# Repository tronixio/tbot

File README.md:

# DRAFT - TBOT 2 Wheels.

## Features.

- 2 Wheels.
- Continuous Servos Motors.
- Power 2xCells 18650 Lithium Ion Rechargeable Batteries, with charger embedded.
- [PARALLAX Small Robot Chassis.](https://www.parallax.com/product/700-00022)
- [PARALLAX Small Robot Whell and Tire.](https://www.parallax.com/product/28114)
- [PARALLAX 1" Tail Whell Ball.](https://www.parallax.com/product/700-00009)
- [PARALLAX Feedback 360 High Speed Servo.](https://www.parallax.com/product/900-00360)

## Kicad.

- [Charger 2x18650.](./0.kicad/charger)
- [TODO - MCU Board.](./0.kicad/mcu)
- [TODO - IR Line Follow.](./0.kicad/ir-line)

## Charger top.

## Charger bottom.

## Notes.

- TODO : Work in progress, prototype was not good, hardware, PCB and code can be rework.
- DRAFT : Prototype OK, last check schematic, PCB & code can be modify.

## DISCLAIMER.

THIS CODE IS PROVIDED WITHOUT ANY WARRANTY OR GUARANTEES.
USERS MAY USE THIS CODE FOR DEVELOPMENT AND EXAMPLE PURPOSES ONLY.
AUTHORS ARE NOT RESPONSIBLE FOR ANY ERRORS, OMISSIONS, OR DAMAGES THAT COULD
RESULT FROM USING THIS FIRMWARE IN WHOLE OR IN PART.

---

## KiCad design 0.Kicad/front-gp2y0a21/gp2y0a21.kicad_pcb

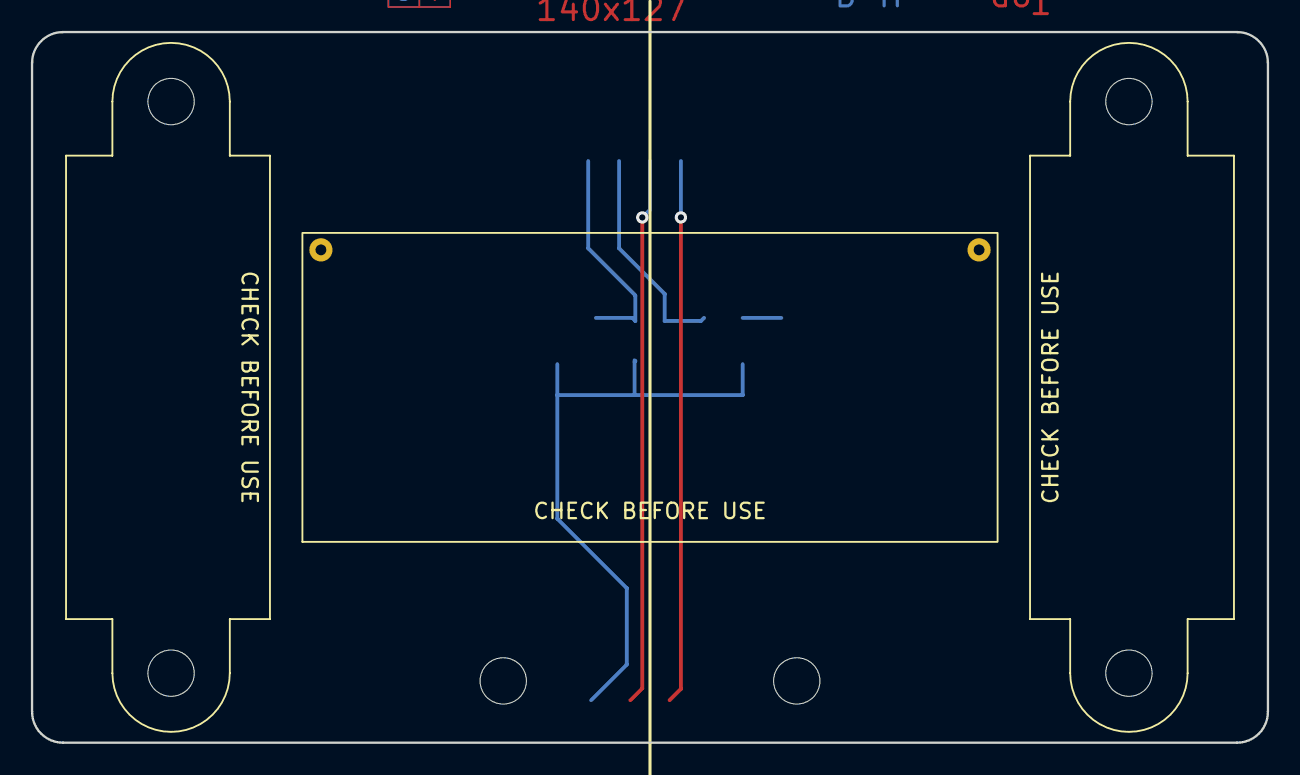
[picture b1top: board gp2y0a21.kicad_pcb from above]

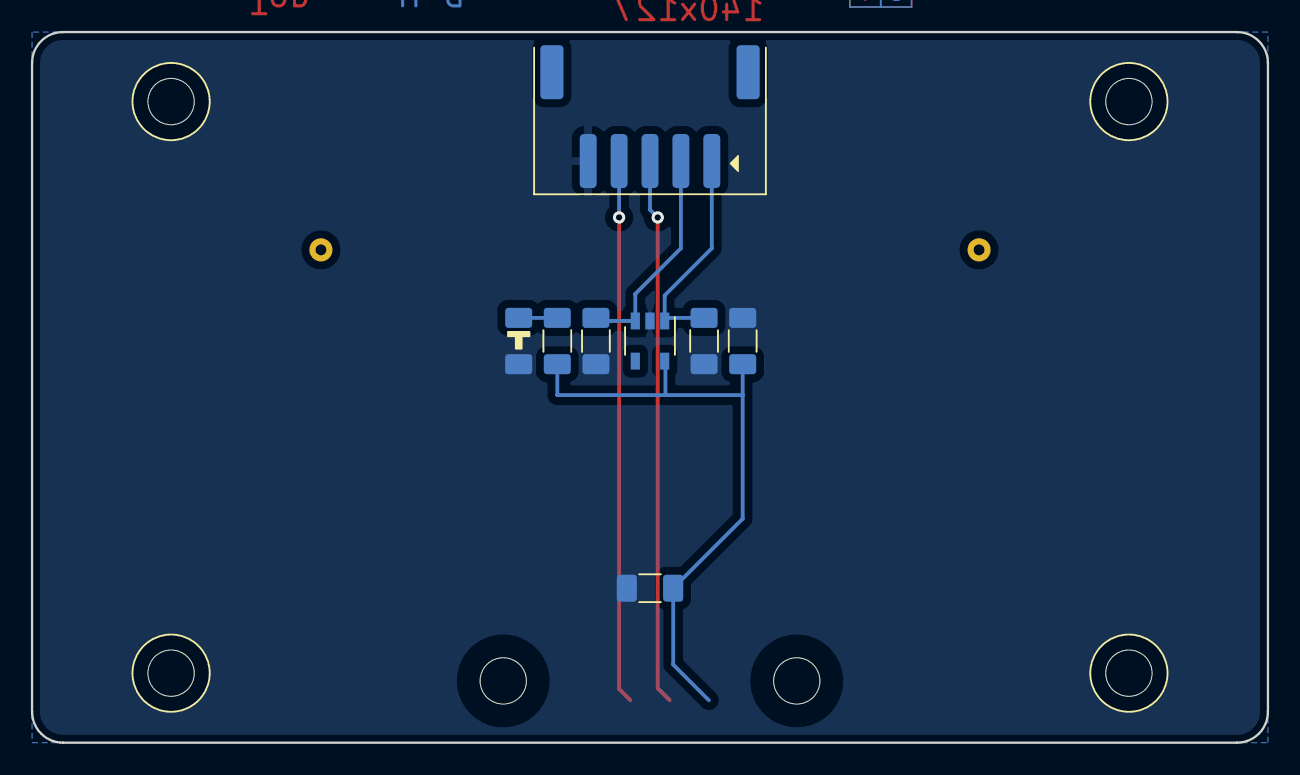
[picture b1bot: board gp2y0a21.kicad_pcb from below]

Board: 2 copper layers, 80.0 x 46.0 mm, 13 parts (8 on the bottom side), 5 nets.

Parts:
C1, C2, C3: C; CAPACITOR_1206
H1, H2: MOUNTING-HOLE-MASK-3MM; M3-MASK
HC1: HC-SR04
IC1: MCP1755-SOT23; SOT-23-5
IR1: SHARP-GP2Y0A21
IR2: SHARP-GP2Y0A41; SHARP-GP2Y0A21
K1: JST-PH-S5B-SM4-TB; JST-S5B-PH-SM4-TB
LED1: LED; LED_1206
R1, R2: R; RESISTOR_1206

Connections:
+5V: C2.1, IC1.5 (VOUT), R2.1
ENABLE: IC1.3 (~SHDN), K1.2, R1.1
GND: C1.2, C2.2, C3.2, IC1.2 (GND), K1.5, LED1.1 (K), R1.2
unnamed: LED1.2 (A), R2.2
VCC: C1.1, IC1.1 (VIN), K1.1

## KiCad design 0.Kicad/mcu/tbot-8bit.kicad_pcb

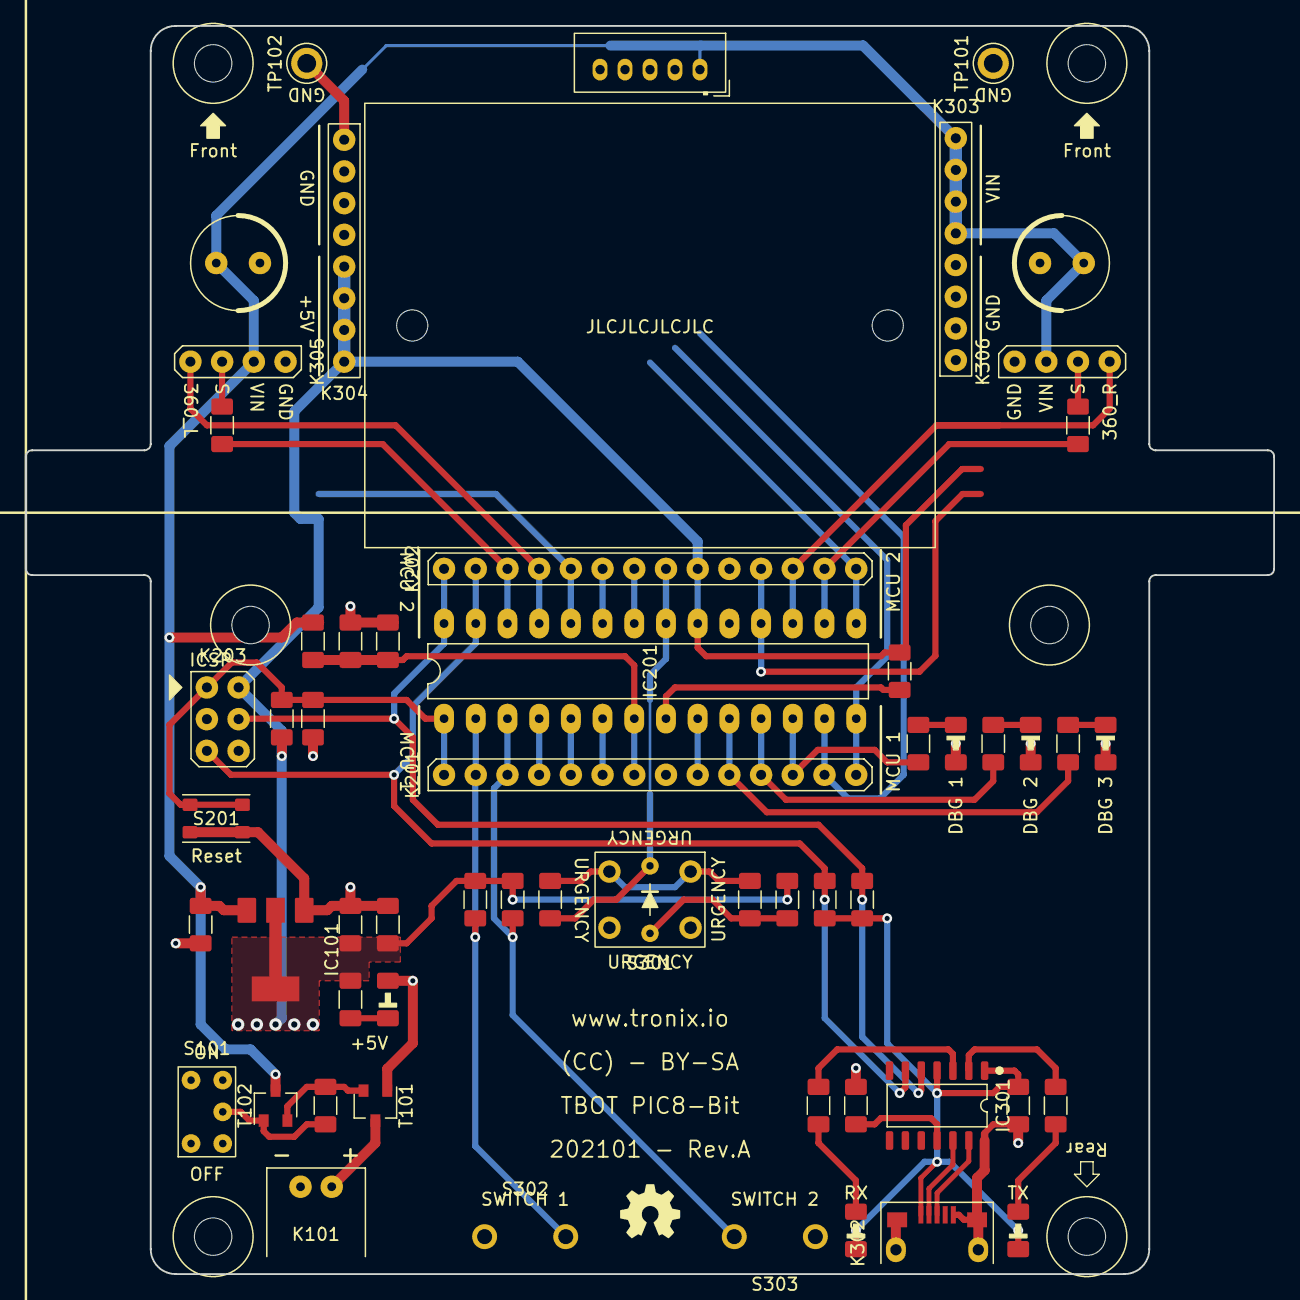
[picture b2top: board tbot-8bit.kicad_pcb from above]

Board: 2 copper layers, 100.0 x 100.0 mm, 64 parts (0 on the bottom side), 43 nets.

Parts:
BB301: BREADBOARD-170
C101, C102, C103, C104, C201, C202: C; CAPACITOR_1206
C301: 100n; CAPACITOR_1206
C302: 470n; CAPACITOR_1206
C303, C304: UVZ-220U-25V; CAPACITOR-ELECTROLYTIC-RADIAL-080-115-035
H1, H2, H3, H4, H5, H6: MOUNTING-HOLE-MASK-3MM; M3-MASK
IC101: TLV1117-50; SOT-223-3
IC201: PIC16F1778-IP; DIP-28-W762
IC301: MCP2221A-ISL; SOIC-SL-14
K101: MOLEX-5268-02
K201, K202: M20-999144x
K203: M20-998034x
K301: FRONT; JST-PH-B5B-K
K302: MICRO USB B; FCI-USB-TYPE-B-MICRO-THT
K303, K304: M20-782084x
K305: SERVO LEFT; M20-999044x
K306: SERVO RIGHT; M20-999044x
LED101: LED; LED_1206
LED301: URX; LED_1206
LED302: UTX; LED_1206
LED303: LED 3; LED_1206
LED304: LED 2; LED_1206
LED305: LED 1; LED_1206
R101, R102, R103, R104, R201, R303, R304, R307: R; RESISTOR_1206
R301, R302, R310, R311: 10K; RESISTOR_1206
R305, R306, R312, R313, R314: 5K6; RESISTOR_1206
R308, R309: 220R; RESISTOR_1206
S101: E-SWITCH-200USP1T1A1M2RE; E-SWITCH-200USPXT1A1M2RE
S201: ALPS-SKRPAC
S301: URGENCY; E-SWITCH-TL1240XQ1JXXX
S302: SWITCH 1; CK-PTS635S-THT
S303: SWITCH 2; CK-PTS635S-THT
T101, T102: DMP2305U; SOT-23-3
TP101, TP102: GND; KEYSTONE-5006

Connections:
+5V: C103.1, C104.1, C201.1, IC101.2 (VO), IC201.20 (VDD), K202.9, K203.2, K304.1, K304.2, K304.3, K304.4, R104.2, R201.2, R303.2, R310.2, R311.2
BATTERY_SENSE: C101.1, IC201.7 (RA5), K201.7, R101.1, R103.2
GND: C101.2, C102.2, C103.2, C104.2, C201.2, C202.2, C301.2, C302.2, C303.2, C304.2, IC101.1 (GND), IC201.8 (VSS), IC201.19 (VSS), IC301.14 (VSS), K101.1, K201.8, K202.10, K203.3, K301.5, K302.5 (GND), K302.6 (SHIELD), K303.5, K303.6, K303.7, K303.8, K304.5, K304.6, K304.7, K304.8, K305.1, K306.1, LED101.1 (K), LED303.1 (K), LED304.1 (K), LED305.1 (K), R103.1, S101.1, S201.1, S201.2, S301.3, S301.4, S302.1, S303.1, T101.1 (G), TP101.1, TP102.1
unnamed: C302.1, IC301.11 (VUSB)
unnamed: IC201.4 (RA2), K201.4
unnamed: IC201.5 (RA3), K201.5
unnamed: IC201.6 (RA4), K201.6
unnamed: IC201.9 (RA7/CLKI), K201.9
unnamed: IC301.2 (GP0), R306.1
unnamed: IC301.3 (GP1), R305.1
unnamed: IC301.12 (D-), K302.2 (D-)
unnamed: IC301.13 (D+), K302.3 (D+)
unnamed: K305.3, R308.2
unnamed: K306.3, R309.2
unnamed: LED101.2 (A), R104.1
unnamed: LED301.1 (K), R305.2
unnamed: LED302.1 (K), R306.2
unnamed: LED303.2 (A), R312.1
unnamed: LED304.2 (A), R313.1
unnamed: LED305.2 (A), R314.1
unnamed: R102.1, S101.2, T102.1 (G)
unnamed: R102.2, T101.2 (S), T102.2 (S)
unnamed: R303.1, R304.2, S301.6 (A)
unnamed: R304.1, R307.1, S301.1, S301.2
RA0/SWITCH_1: IC201.2 (RA0), K201.2, R310.1, S302.2
RA1/SWITCH_2: IC201.3 (RA1), K201.3, R311.1, S303.2
RA7/LED_3: IC201.10 (RA6/CLKO), K201.10, R312.2
RB0/URGENCY: IC201.21 (RB0), K202.8, R307.2, S301.5 (C)
RB4/360_L: IC201.25 (RB4), K202.4, K305.4
RB5/SERVO_L: IC201.26 (RB5), K202.3, R308.1
RB6/PGC/URX: IC201.27 (PGC/RB6), IC301.6 (UTx), K202.2, K203.5, R302.1
RB7/PGD/UTX: IC201.28 (PGD/RB7), IC301.5 (URx), K202.1, K203.4, R301.1
RC0/LED_2: IC201.11 (RC0), K201.11, R313.2
RC1/LED_1: IC201.12 (RC1), K201.12, R314.2
RC2/ENABLE: IC201.13 (RC2), K201.13, K301.2
RC3/TRIGGER/SCL: IC201.14 (RC3), K201.14, K301.3
RC4/ECHO/SDA: IC201.15 (RC4), K202.14, K301.4
RC5/SERVO_R: IC201.16 (RC5), K202.13, R309.1
RC6/360_R: IC201.17 (RC6), K202.12, K306.4
VBAT: K101.2, T101.3 (D)
VIN: C102.1, C303.1, C304.1, IC101.3 (VI), K301.1, K303.1, K303.2, K303.3, K303.4, K305.2, K306.2, R101.2, T102.3 (D)
VUSB: C301.1, IC301.1 (VDD), IC301.4 (~RESET), K302.1 (VBUS), LED301.2 (A), LED302.2 (A), R301.2, R302.2
~MCLR: C202.1, IC201.1 (RE3/~MCLR), K201.1, K203.1, R201.1, S201.3, S201.4

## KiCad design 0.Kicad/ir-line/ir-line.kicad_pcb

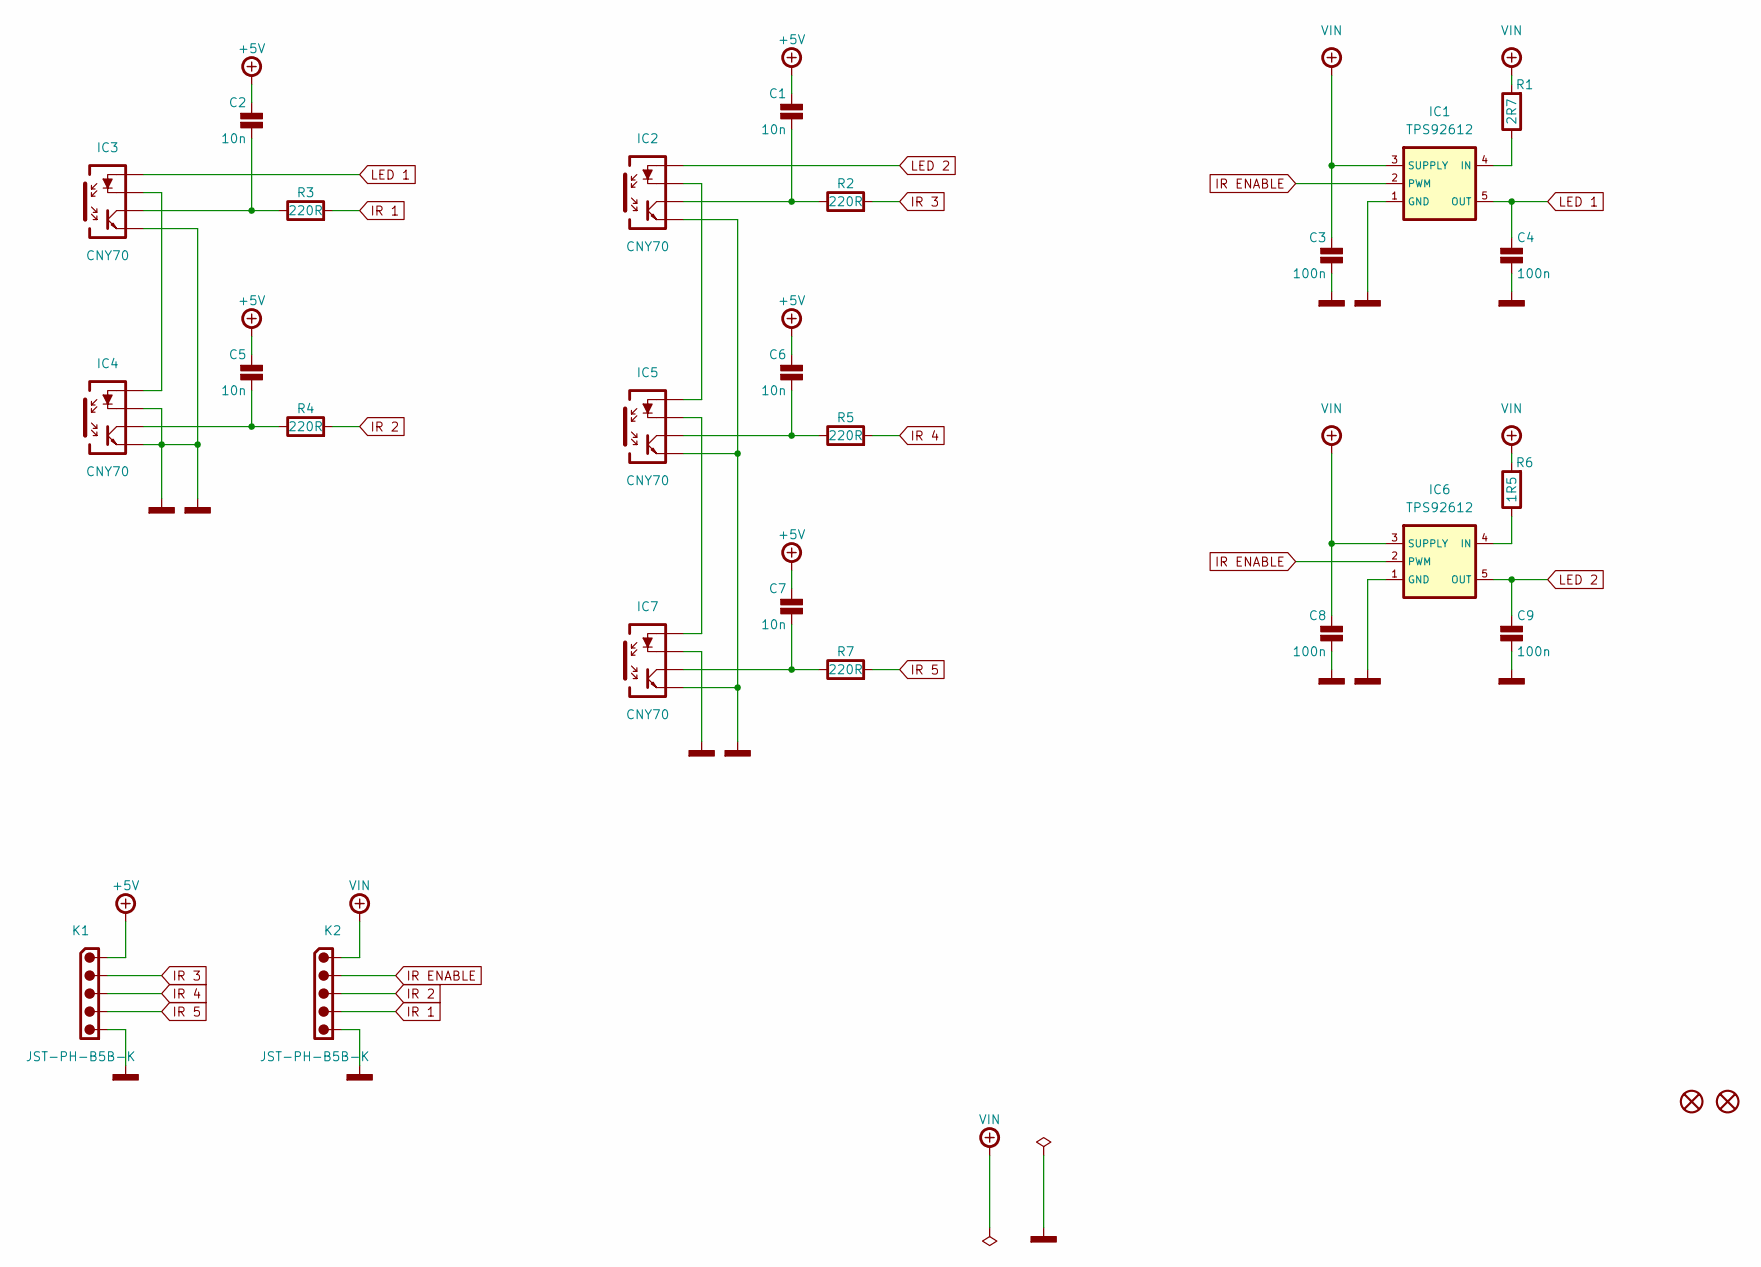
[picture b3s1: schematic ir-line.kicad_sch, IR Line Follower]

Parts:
C1, C2, C5, C6, C7: 10n; CAPACITOR-1206
C3, C4, C8, C9: 100n; CAPACITOR-1206
H1, H2: MOUNTING-HOLE-MASK-3MM; M3-MASK
IC1, IC6: TPS92612; SOT-23-5
IC2, IC3, IC4, IC5, IC7: CNY70; VISHAY-CNY70
K1, K2: JST-PH-B5B-K
R1: 2R7; RESISTOR-1206
R2, R3, R4, R5, R7: 220R; RESISTOR-1206
R6: 1R5; RESISTOR-1206

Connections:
+5V: C1.1, C2.1, C5.1, C6.1, C7.1, K1.1
GND: C3.2, C4.2, C8.2, C9.2, IC1.1 (GND), IC2.3 (E), IC3.3 (E), IC4.1 (K), IC4.3 (E), IC5.3 (E), IC6.1 (GND), IC7.1 (K), IC7.3 (E), K1.5, K2.5
IR 1: K2.4, R3.2
IR 2: K2.3, R4.2
IR 3: K1.2, R2.2
IR 4: K1.3, R5.2
IR 5: K1.4, R7.2
IR ENABLE: IC1.2 (PWM), IC6.2 (PWM), K2.2
LED 1: C4.1, IC1.5 (OUT), IC3.4 (A)
LED 2: C9.1, IC2.4 (A), IC6.5 (OUT)
unnamed: C1.2, IC2.2 (C), R2.1
unnamed: C2.2, IC3.2 (C), R3.1
unnamed: C5.2, IC4.2 (C), R4.1
unnamed: C6.2, IC5.2 (C), R5.1
unnamed: C7.2, IC7.2 (C), R7.1
unnamed: IC1.4 (IN), R1.1
unnamed: IC2.1 (K), IC5.4 (A)
unnamed: IC3.1 (K), IC4.4 (A)
unnamed: IC5.1 (K), IC7.4 (A)
unnamed: IC6.4 (IN), R6.1
VIN: C3.1, C8.1, IC1.3 (SUPPLY), IC6.3 (SUPPLY), K2.1, R1.2, R6.2

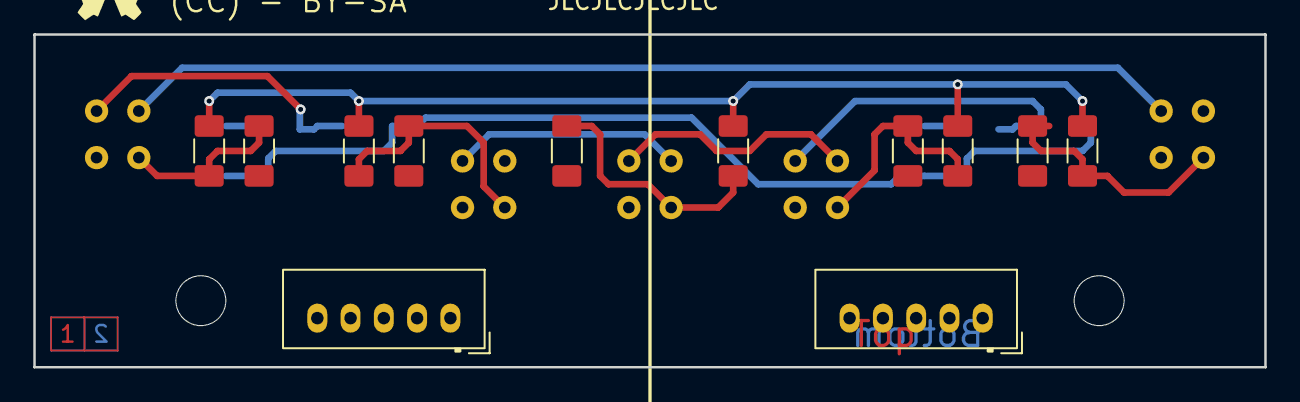
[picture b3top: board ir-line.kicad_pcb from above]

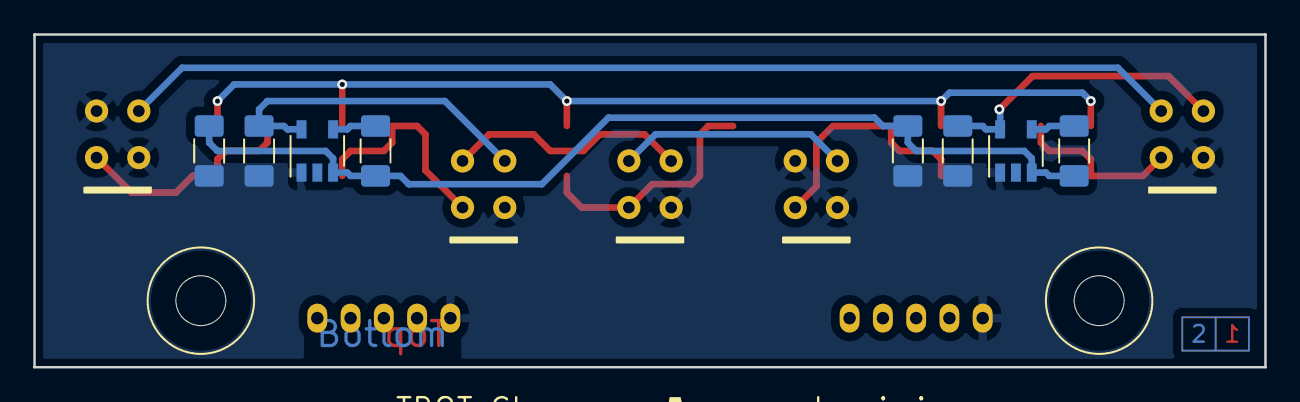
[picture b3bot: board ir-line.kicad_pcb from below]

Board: 2 copper layers, 74.0 x 20.0 mm, 27 parts (15 on the bottom side), 21 nets.

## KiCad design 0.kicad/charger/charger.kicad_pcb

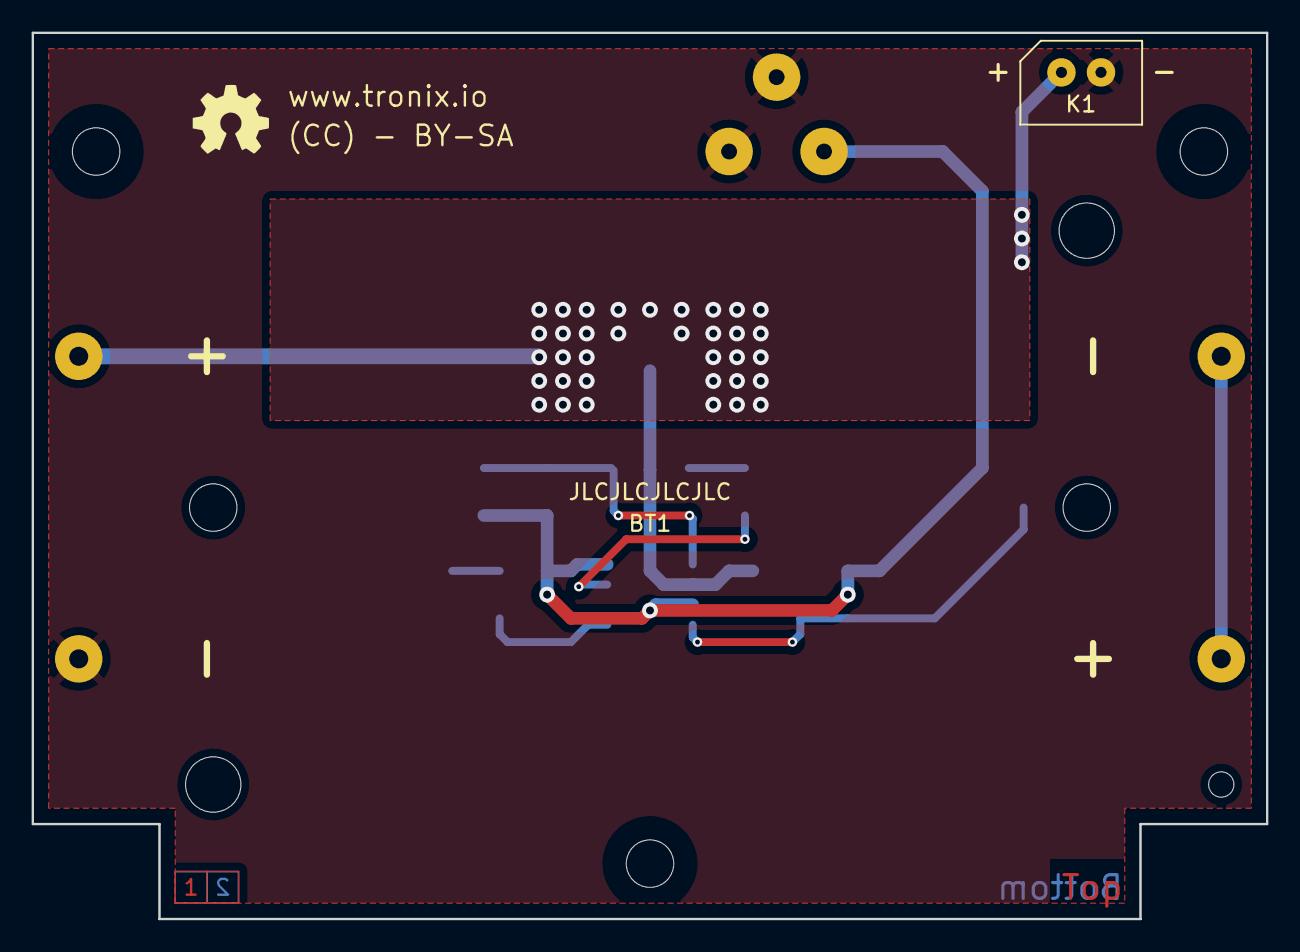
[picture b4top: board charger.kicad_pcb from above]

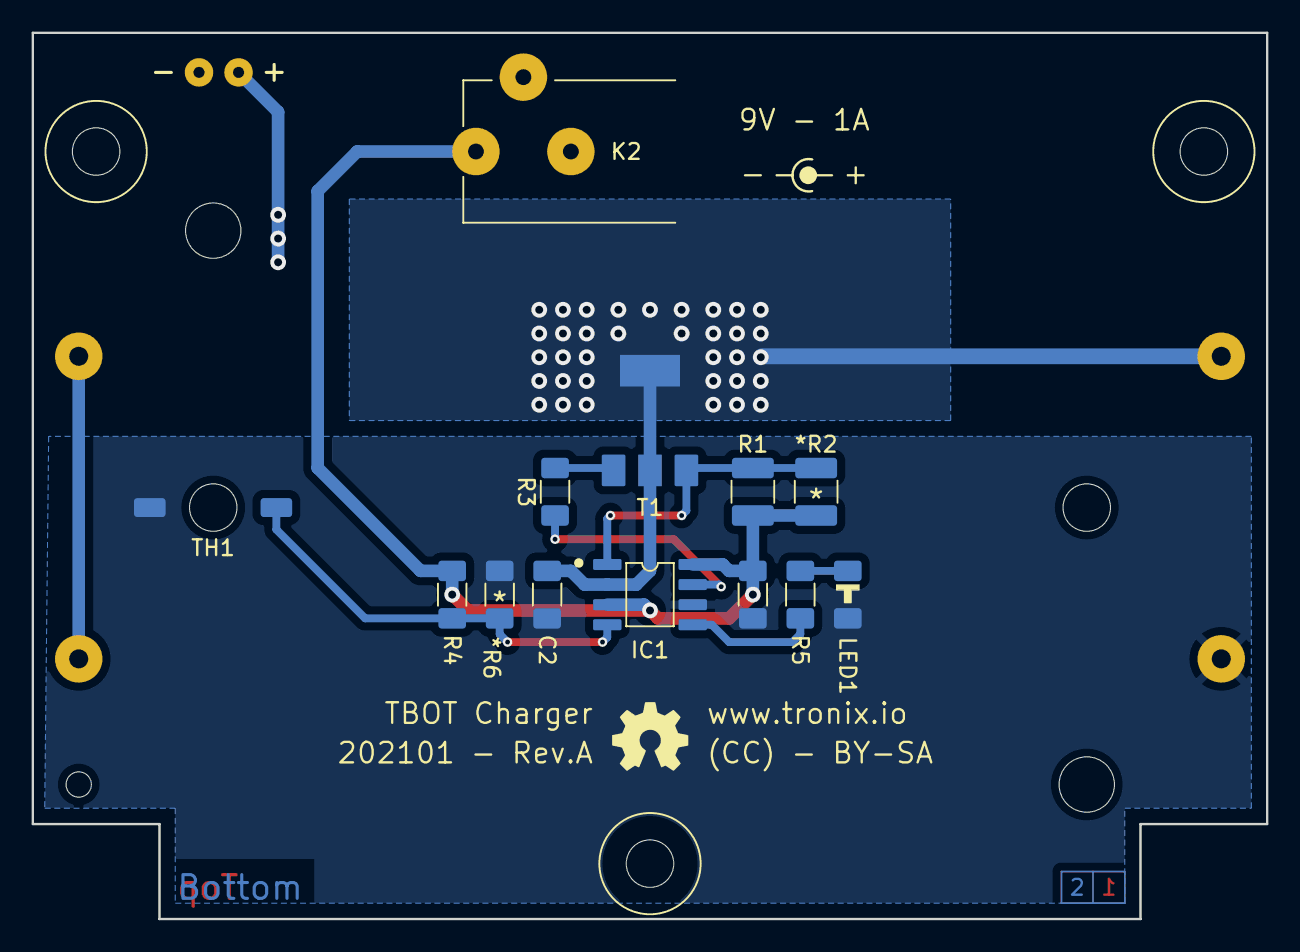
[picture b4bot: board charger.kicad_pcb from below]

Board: 2 copper layers, 78.0 x 56.0 mm, 18 parts (16 on the bottom side), 10 nets.

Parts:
*R2: 0R1; RESISTOR_1210
*R6: 36K; RESISTOR_1206
BT1: 18650; KEYSTONE-1049
C1: 100n; CAPACITOR_1206
C2: 1µ; CAPACITOR_1206
H1, H2, H3: MOUNTING-HOLE-MASK-3MM; M3-MASK
IC1: BQ2057W; SOIC-8
K1: Battery; MOLEX-5267-02
K2: Charge; CUI-PJ-102AH
LED1: Charge; LED_1206
R1: 0R1; RESISTOR_1210
R3: 1K; RESISTOR_1206
R4: 10K; RESISTOR_1206
R5: 5K6; RESISTOR_1206
T1: STN790A; SOT-223-3
TH1: 10K; THERMISTOR

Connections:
GND: *R6.1, BT1.3 (-), C1.2, C2.2, IC1.6 (VSS), K1.1, K2.2, K2.3, LED1.1 (K), TH1.2
unnamed: *R2.2, IC1.1 (SNS), R1.2, T1.3 (E)
unnamed: *R6.2, IC1.4 (TS), R4.1, TH1.1
unnamed: BT1.1 (-), BT1.4 (+)
unnamed: IC1.5 (STAT), R5.2
unnamed: IC1.7 (CC), R3.1
unnamed: LED1.2 (A), R5.1
unnamed: R3.2, T1.1 (B)
VBAT: BT1.2 (+), C2.1, IC1.2 (BAT), K1.2, T1.2 (C)
VCC: *R2.1, C1.1, IC1.3 (VCC), IC1.8 (COMP), K2.1, R1.1, R4.2
